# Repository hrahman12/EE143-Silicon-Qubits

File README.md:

# Atom-by-Atom Silicon: Building Quantum Processors from Single Dopant Atoms

EE143 (Microfabrication Technology) tutorial deck, 15 min. A device profile of STM-patterned P and As dopant qubits, featuring the work of Neil J. Curson (UCL).

- **Deck:** `deck/atom_by_atom_silicon.pptx` (editable, 16:9, 10 × 5.625 in) and `deck/atom_by_atom_silicon.pdf`
- **Speaker notes:** in the .pptx and in `notes/speaker_notes.md` (with a 15-minute timing plan)
- **Facts:** every number comes from `REFERENCES.md` (transcribed from `notes/reference_pack.pdf`); see `qa/fact_check.md`

## Rebuild

```bash
npm install                                  # pptxgenjs 3.12.0, image-size 1.1.1
pip install matplotlib numpy pillow pymupdf  # figure scripts
python3 figures/src/make_figures.py          # crops + original diagrams -> figures/final/
npm run build                                # node build_deck.js, strip zip folder entries, export PDF (needs LibreOffice)
```

QA render: `pdftoppm -jpeg -r 110 deck/atom_by_atom_silicon.pdf qa/render/s` (renders are git-ignored).

### Re-downloading raw figures
`python3 figures/src/fetch_pmc.py` pulls figure images, article XML (licence text) and metadata from the PMC Open Access bucket. The article PDFs are git-ignored to keep the repo small; the images extracted from them (`figures/raw/*/pdfimg/`, `page*_300dpi.png`) are committed. To re-extract, download:
- PMC PDFs: `https://pmc-oa-opendata.s3.amazonaws.com/<PMCID>.1/<PMCID>.1.pdf`
- Schofield2025: `https://arxiv.org/pdf/2501.04535v2`
- DAnna2023: UCL Discovery 10167842 (CC BY published version)

## Simulations and animations
`npm run sim` (QuTiP 5) runs `figures/src/simulate_qubits.py`:
- fits the Reiner2024 donor Hamiltonian to the 14 ESR/NMR lines of Thorvaldson2025, recovering A = 6.05/67.97/102.99 MHz;
- simulates the conditional Rabi drive and Grover search;
- renders the fabrication, yield Monte Carlo and cover animations.

Animated GIFs play in PowerPoint and Keynote; the PDF shows each first frame. `qa/add_transitions.py` adds fade transitions after the build. No real quantum hardware was run.

## Web preview
`python3 qa/build_preview.py <dir>` composites each embedded GIF into its LibreOffice slide render (animated WebP) and writes `slides.json`. That folder plus `index.html` is the published preview page, republished after each deck change.

## Layout system
`build_deck.js` defines the theme once (Arial; ink #1F2A36, muted #5B6770, P #D9731A, As #0F9FA0, fixed material legend) and eight slide masters (TITLE, SECTION, TITLE_ONLY, FIG_TEXT, TWO_FIG, TABLE, PROCESS, REFS) with named `title` and `src` placeholders, footer and slide number. Sections: Intro, Motivation, Process, Results, Scaling, Prototype, Wrap-up, Backup. Charts (array yield, write speed on a log axis, Poisson ion statistics, thermal budget) are native PowerPoint charts.

## Story and slides (four acts)
Intro → Act 1 Why single atoms → Act 2 How it is built → Act 3 Does it work → Act 4 How it scales → Wrap-up. Each slide carries an act label.

## Exact paper specs
Diagrams are drawn from verbatim specs collected in `notes/specs/` (one table per paper group, each value with its quote and location): to-scale D'Anna 2023 stack, Stock 2020 Fig. 4e temperature program, Si(001) geometry (a = 3.84 Å, dimer bond 2.357 Å, Si–H 1.51 Å), Schofield 2003 sites, Kane 2000 operating point, prototype layout from Stock 2024 + Edlbauer 2025. New sources beyond the pack: Jakob2022, Reiner2024, Namboodiri2024, DAnna2026, Kiczynski2022, Kane2000, OBrien2001, Ren2016, Xiang2025 (see `notes/specs/additional_sources.md`).

## Slides (original outline, now reordered)
1 Title · 2 Device at a glance · 3 Timeline · 4 Why a donor · 5 Why not implantation · 6 Neil J. Curson · 7 11-step process flow (EE143 module per step) · 8–13 Steps 1–11 (cross-section + legend + step tracker) · 14 Did it work (+ EE143 sheet-resistance check) · 15 Landmarks · 16 Yield problem (+ Monte Carlo) · 17 Arsenic fix · 18 Beyond Si:P · 19 Processors · 20 Simulator · 21 Throughput wall · 22 EUV scaling · **23 Our prototype (3D render + yield model)** · **24 Prototype traveler mapped to EE143** · 25 Takeaways · 26 References · Backup: alternate titles

Slides 23–24 go beyond the outline: an original 2×2 As register design and its traveler, built only from published recipes.

## Reproduced vs original images
**Reproduced (CC BY 4.0, credited on the slide):** Stock2024 Figs. 1, 3; Schofield2025 §2.2, §2.4, §3.2, §4.1, §5.3 figures; Constantinou2024 Fig. 5; Constantinou2023 Fig. 2; D'Anna2023 Fig. 2; Stock2020 Figs. 3, 4; Hofmann2023 Fig. 1a; Lundgren2023 Fig. 1; Thorvaldson2025 Fig. 4b; Edlbauer2025 Fig. 1a,b; Wang2022 Fig. 1. Licences were checked in each article's own XML; Stock2020 (ACS AuthorChoice CC-BY) and Tseng2023 (CC BY 4.0) included.

**Original (code in `figures/src/make_figures.py`, or native shapes and charts):** Kane-style cross-section (after Kane1998), 3D Si(001):H surface renders, step cross-sections, process icons, overgrowth temperature program, spin-level diagram, 2003/2012 landmark schematics (after Schofield2003 / Fuechsle2012), Monte Carlo array outcomes, 3D yield surface, prototype 3D render, timelines, all charts. No paywalled or CC BY-NC-ND figure is embedded, and no micrograph or data plot is generated. Full list: `figures/manifest.csv`.

## QA status
- Rendered with LibreOffice and checked slide by slide (overflow, overlaps, margins, title position).
- Anthropic pptx-skill `validate.py`: all validations passed.
- Speaker notes: 98–130 words on every slide.
- `qa/fact_check.md`: every number on the slides mapped to its Key-numbers row and key; derived values marked.
- `qa/text_dump.txt`: full text and notes dump via python-pptx.

## Open items
See `qa/open_items.md`. Main ones: the `reference_decks/` folder wasn't supplied, so style comes from the measurements in the reference pack; confirm the talk date (shown as "Fall 2026"); and a few outline items had no source and were left off.

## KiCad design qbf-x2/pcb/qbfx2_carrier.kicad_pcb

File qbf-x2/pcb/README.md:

# QBF-X2 cryogenic RF carrier PCB (rev B, 2026-11-26)

A 6-layer Rogers RO4003C / RO4450F carrier for the 10 x 10 mm QBF-X2 superconducting die. The die sits in a
10.30 mm through-window on a pedestal of the copper sample-holder base, with its top
flush with the board. It is wire bonded to 32 landing pads that follow `../circuits/die_pads.json` (rev B), the
chip-to-board contract.

- **8 fast flux lines = 8 differential pairs** (`<name>_P` / `<name>_N`, 16 SMP jacks). On the chip each fast line is
  one floating loop: P runs out along its rail, N comes back on the far side of the launch strip, with no ground
  return. Each leg is driven by its own 50-ohm coax from complementary AWG outputs.
- **2 readout lines** (RO_IN, RO_OUT): single-ended 50-ohm grounded CPW, unchanged from rev A.
- **8 DC lines**: striplines on In2 to on-board RC filters next to a micro-D connector (J11), unchanged in function.

All RF lines are mask-free grounded CPW on the top layer over the solid In1 plane. Everything is generated by Python
from `carrier_params.py`; nothing was drawn by hand. KiCad 7.0.11 (`kicad-cli` and the `pcbnew` module) fills the
zones, runs DRC and writes every fabrication output.

| | |
|---|---|
| Board | 66 x 66 mm (rev A: 52 x 52), 1.50 mm, 6 Cu layers, through vias only |
| Parts | 52 schematic parts (47 on the PCBA), 5 board-only (3 fiducials, 2 dowel holes) |
| Nets | 43: 16 fast-line legs (8 pairs), 2 readout, 24 DC (8 die-side, 8 connector-side, 8 filter nodes), GND |
| Vias | 1421: 1393 GND stitching / fences / launch cages, 16 DC transitions, 12 filter-cap GND |
| DRC (pcbnew 7.0.11) | **0 violations, 0 unconnected, 0 footprint errors** (KiCad's own diff-pair, skew and length rules included) |
| Schematic vs PCB | **0 mismatches** (52 components, 144 pads) |
| Differential pairs | Z_odd 51.9 ohm (closed form) / 47.9 ohm (2D field solve, 35 um Cu); field solve: Z_diff 95.8 ohm, Z_even 51.4 ohm, Z_cm 25.7 ohm, k = 0.035 |
| Intra-pair skew | max 0.0002 mm = 0.0011 ps (limit 0.10 mm ~ 0.5 ps) |
| A/B pair match | max 0.0002 mm (limit 0.20 mm) |
| Single-ended GCPW | rf_calc formula 51.98 ohm; 2D field solve (35 um Cu) 47.66 ohm; target 50 +/-5 % |
| Filters | gate 596 Hz (<= 10 kHz); load 17.7 MHz into the load loop, 8.84 MHz open |

## What changed from rev A

| | rev A | rev B |
|---|---|---|
| Die contract | 24 pads, 8 single-ended fast lines | 32 pads (`circuits/die_pads.json` rev B): 8 P/N pad pairs, 0.50 mm apart, 1.40 mm between pair centres |
| Fast lines | 50-ohm GCPW to 8 SMP jacks | edge-coupled GCPW pairs to 16 SMP jacks (two per pair, side by side) |
| Board | 52 x 52 mm | 66 x 66 mm; SMP columns at x = +/-26.5 mm, 8 jacks per side at a 6.5 mm pitch |
| Filter bank / J11 | channel vias at y = 9, J11 at y = 19 | moved north (vias y = 16, J11 y = 26) to clear the TRAP pairs; same circuit and routing topology |
| Designators | SMP J1-J10, micro-D J11 | SMP J1-J10 and J12-J19 (18 jacks), micro-D stays J11 |
| DRC rules | A/B skew groups | per-pair width / gap / uncoupled / skew rules plus A/B length windows (below) |

The reason for the change is on the chip: a fast line that is one floating loop has no ground return, so its
crosstalk into the other rail of the same qubit drops from 9-17 % to 5.5-7 % (2D cross-section solve of the die),
and common-mode / ground-loop current cannot drive flux through it.

## Files

| Path | What |
|---|---|
| `carrier_params.py` | single source of truth: geometry, stackup, rules, pair geometry, filter values, parts |
| `build_carrier.py` + `carrier_lib/` | writes the KiCad project from scratch (schematic, libraries, 3D models, routed board, rules) |
| `carrier_lib/diffpair.py` | differential-pair geometry: concentric bends, symmetric opening, arc-only tuning bumps, split, KiCad 7 coupling helpers |
| `carrier_lib/fd2d.py` | 2D field solver (single GCPW and odd/even modes of the coupled pair) and the coupled closed-form estimate |
| `finalize_carrier.py` | KiCad zone fill + DRC (pcbnew) |
| `check_carrier.py` | schematic-vs-PCB, ERC substitute, impedance (single-ended and pairs), lengths and skew, filters, DRC fault injection |
| `make_outputs.py`, `render_3d.py`, `make_readme.py` | BOM, drawings, previews, 3D renders, this README |
| `export_carrier.sh` | runs everything: rebuilds every file below |
| `qbfx2_carrier.kicad_pro/.kicad_sch/.kicad_pcb/.kicad_dru` | the KiCad 7 project (zones filled) |
| `qbfx2.kicad_sym`, `qbfx2.pretty/`, `sym-lib-table`, `fp-lib-table`, `3dmodels/` | project libraries (inline copies are in the sheet and the board) |
| `fab/gerbers/` | Gerber X2: 6 copper, 2 mask, 2 paste, 2 silk, Edge.Cuts, fab-notes layer, `.gbrjob` |
| `fab/drill/` | Excellon PTH + NPTH (mm, origin = board lower-left) and drill-map PDFs |
| `fab/assembly/qbfx2_carrier-pos.csv` | pick-and-place (mm, both sides, origin = board lower-left) |
| `fab/qbfx2_carrier_bom.csv` | BOM with manufacturer, MPN, MPN status |
| `fab/qbfx2_carrier-schematic.pdf` | schematic (A3) |
| `fab/qbfx2_carrier-fab_drawing.pdf` | fabrication drawing: outline + dimensions, stackup, impedance and drill tables, fab notes, then drill maps |
| `fab/qbfx2_carrier-assembly.pdf` | assembly drawing: 2:1 top detail, wire-bond diagram, notes, BOM summary, J11 pinout, RF lengths |
| `fab/qbfx2_carrier.step` | 3D STEP of the assembled board (KiCad export with the generated OCP models) |
| `fab/qbfx2_carrier.net` | schematic netlist (KiCad s-expression) |
| `fab/previews/` | PNG previews: top/bottom, each copper layer, die area, In2 routing, drawings, 3D renders |
| `reports/` | DRC report, all check reports, `check_summary.json`, build model, logs |

## Board

**Die interface.** U1 has one landing pad per die pad, pads 1-32 = die launcher ids, 0.10 mm
from the window edge and laterally aligned with the die pads, so every bond is straight (0.77 mm from
the die pad centre to the bond foot, angle 0.0 deg). The lands of the differential pairs are
0.29 x 0.60 mm on the die's 0.50 mm pitch (P-N gap 0.21 mm,
gap to ground 0.17 mm; minimum clearance 0.15 mm); all other lands are
0.39 x 0.60 mm. The window is 10.30 mm (0.15 mm clearance),
with R0.60 corner reliefs. The ground between landing pads is exposed (F.Mask openings over GND only)
for ground bonds where the strip is wide enough: on the N/S rows, at the corners and between each TRAP pair and its LOAD
land. Between two pairs the ground strip at the lands is only 0.27 mm wide, so it stays under mask (the fast lines are
floating loops on the chip and do not return through the die ground).

**Differential pairs (8 fast flux lines).**
- Cross-section (routed): two legs w 0.39 mm, P-N gap 0.65 mm (leg pitch 1.04 mm), gap
  0.17 mm to the coplanar ground, over 0.203 mm RO4003C to the In1 plane. No ground copper and no vias between
  P and N: an F.Cu keepout per pair (`DIFF_<pair>_no_gnd_no_via`) blocks the pour and vias; the via fences run on the
  outside of each pair only.
- Loose coupling on purpose: each leg is a 50-ohm line for its own coax, so Z_odd = 50 ohm and Z_even stays near 50 ohm
  (k = 0.035). The legs use the same width and ground gap as the single-ended lines, so the split into two
  single-ended legs at the jacks is a smooth transition.
- Breakout at the die: the die pads are 0.50 mm apart and the pairs 1.40 mm apart, which leaves no room for the routed
  cross-section. From the lands to the first bend each pair runs as w 0.29 / gap 0.21 mm (leg pitch 0.50 mm,
  so the lands and the coupled pair line up and the bonds stay straight). Right after the first bend both legs make
  mirror-image S-jogs (R 1.0 mm) out to the routed spacing and the width steps to 0.39 mm.
- Route (west-top quadrant; the others are mirror images): straight breakout, bend B1 away from the die axis
  (60.3 deg for TRAP, 45 deg for ACC; the TRAP angle is tan = 7/4 so that both legs lie on an exact nm lattice),
  diagonal, bend B2 back to the die-normal direction, straight, then the split: each leg turns away from its partner
  (45-degree jogs, R 1.0 mm) and runs straight into its own SMP jack. Every bend is a pair of concentric
  tangent arcs (inner leg radius R - c/2, outer R + c/2), so the pair stays symmetric through the bend.
- Jacks: two SMP jacks per pair, side by side 6.5 mm apart in the column at x = +/-26.5 mm
  (ACC pairs at |y| = 3.25 / 9.75 mm, TRAP pairs at |y| = 16.25 / 22.75 mm).
  West column top to bottom: J1 TRAP_A0_P, J2 TRAP_A0_N, J3 ACC_A0_P, J4 ACC_A0_N, J5 ACC_A1_P, J6 ACC_A1_N, J7 TRAP_A1_P,
  J8 TRAP_A1_N; east column: J9 TRAP_B1_P, J10 TRAP_B1_N, J12 ACC_B1_P, J13 ACC_B1_N, J14 ACC_B0_P, J15 ACC_B0_N, J16 TRAP_B0_P,
  J17 TRAP_B0_N. RO_IN = J18, RO_OUT = J19. The pair is coupled from the lands to the split; the split is
  6.54 mm (TRAP) / 6.54 mm (ACC) per leg.
- Length matching: a concentric bend of angle theta at leg pitch c makes the inner leg shorter by c * theta. B1 is taken
  at the breakout pitch (0.50 mm) and B2 at the routed pitch (1.04 mm), so they do not cancel. Each mismatch is
  compensated next to the bend that causes it, with small symmetric arc-only bumps (arcs +a, -2a, +a, R 0.30 mm)
  on the shorter leg, bulging away from its partner: the outer leg right after the opening for B1, the inner leg next to
  B2 (just before it for TRAP, just after it for ACC). TRAP: -60.3 deg at leg pitch 0.50 mm -> TRAP_A0_P short by 0.526 mm; +60.3 deg at leg pitch 1.04 mm -> TRAP_A0_N short by 1.094 mm. Bumps: TRAP_A0_P: 1 x +0.526 mm (height 0.51 mm, span 1.19 mm); TRAP_A0_N: 2 x +0.547 mm (height 0.53 mm, span 1.19 mm). ACC: -45.0 deg at leg pitch 0.50 mm -> ACC_A0_P short by 0.393 mm; +45.0 deg at leg pitch 1.04 mm -> ACC_A0_N short by 0.817 mm.
  Bumps: ACC_A0_P: 1 x +0.393 mm (height 0.43 mm, span 1.15 mm); ACC_A0_N: 2 x +0.408 mm (height 0.44 mm, span 1.16 mm). The running P-N difference returns to zero within 4.9 mm (TRAP) /
  4.3 mm (ACC) of every bend.
- Mask: every leg has its own mask-free corridor (trace + gaps); a 0.14 mm LPI web on the pair centre line separates
  the two (KiCad flags one aperture that exposes two nets). In the routed section that leaves 0.16 mm bare next to each
  leg and LPI on the middle 0.33 mm of the P-N gap; the field solve includes it.

**Readout lines (2).** Single-ended GCPW on F.Cu over the solid In1 plane, w 0.39 mm, gap 0.17 mm,
tangent-arc bends R 1.0 mm, GND vias every 1.0 mm on both sides at 0.625 mm from the line centre, to J18/J19
on the south side. Each SMP has a GND via cage (3 under the body, 9 around it), a 0.75 mm centre pad and a 1.65 mm anti-pad.

**DC lines (8).**
- Each landing pad has a short F.Cu stub to a via, then a 0.15 mm stripline on In2 between the In1 and In3 planes.
- The south lines (GATE_BSB_*) and LOAD_A1/LOAD_B0 reach the north through an In2 corridor under the bond-pad ring; the
  planar order means nothing crosses. Rev B: the LOAD lands moved out to |y| = 3.5 mm, so the bottom LOAD lines now join
  their corridor with a 45-degree segment, clear of the GATE_BSB detour around the window corner.
- They end at 8 filter channels on the top side, next to J11.
- J11 pinout: 1 LOAD_A0, 2 LOAD_A1, 3 GATE_BSB_AN, 4 GATE_BSA_PREP, 5 GATE_BSA_AN, 6 GATE_BSB_PREP, 7 LOAD_B0, 8 LOAD_B1; 9-15 and the shell are GND.

**Mechanics.**
- 4 x M2.5 plated holes (GND) at +/-29.5 mm.
- 2 x 1.60 mm NPTH dowel holes align the window to the base pedestal.
- 3 fiducials.
- The bottom copper is a continuous GND plane; B.Mask is opened 2 mm along the edge for contact with the base.
- The J11 tails and their solder fillets (DC signals) come through to the bottom. The copper base therefore needs a
  relief pocket, at least 1.5 mm deep, under the tail field (x -11..+11 mm, y +24..+30 mm
  from the die centre). Otherwise the DC lines short to ground.

### Stackup (defined in the board file, `setup/stackup`)

| Layer | Type | Material | t (mm) | er | tan d | Use |
|---|---|---|---|---|---|---|
| F.Mask | mask | LPI solder mask | 0.020 | 3.8 | 0.025 | green LPI; open over RF lines + bond band |
| F.Cu | copper | Cu 1 oz (finished) | 0.035 |  |  | RF GCPW, bond pads, parts, GND pour |
| diel1 | core | Rogers RO4003C | 0.203 | 3.55 | 0.0027 | core 1 (8 mil); GCPW dielectric |
| In1.Cu | copper | Cu 0.5 oz | 0.018 |  |  | solid GND: GCPW reference plane |
| diel2 | prepreg | Rogers RO4450F | 0.203 | 3.52 | 0.004 | 2 x 4 mil plies |
| In2.Cu | copper | Cu 0.5 oz | 0.018 |  |  | DC routing (stripline between In1/In3) + GND fill |
| diel3 | core | Rogers RO4003C | 0.508 | 3.55 | 0.0027 | core 2 (20 mil) |
| In3.Cu | copper | Cu 0.5 oz | 0.018 |  |  | solid GND |
| diel4 | prepreg | Rogers RO4450F | 0.203 | 3.52 | 0.004 | 2 x 4 mil plies |
| In4.Cu | copper | Cu 0.5 oz | 0.018 |  |  | solid GND |
| diel5 | core | Rogers RO4003C | 0.203 | 3.55 | 0.0027 | core 3 (8 mil) |
| B.Cu | copper | Cu 1 oz (finished) | 0.035 |  |  | solid GND; contacts the sample-holder base |
| B.Mask | mask | LPI solder mask | 0.020 | 3.8 | 0.025 | opened along the board perimeter (base contact) |

**Why RO4003C:**
- Low loss: tan d 0.0027.
- Stable Dk.
- The glass-reinforced hydrocarbon/ceramic does not cold-flow, unlike PTFE.
- Processes like FR-4, so a symmetric 3-core build needs one lamination and through vias only.
- The room-temperature design Dk 3.55 is used. How Dk and loss change at 10 mK is not modelled here.

## Design rules

The board minima are set in `.kicad_pro`:
- clearance 0.15 mm, track 0.12 mm
- via 0.45 / 0.20 mm, annular ring 0.125 mm
- hole-to-hole 0.25 mm, hole clearance 0.20 mm
- copper-to-edge 0.10 mm (used only at the die window: landing pads and exposed ground band)
- mask web 0.10 mm

Net classes are assigned by pattern:

| Net class | Patterns | Width | Clearance | Diff pair |
|---|---|---|---|---|
| RF_DIFF | TRAP_*, ACC_* | 0.39 mm | 0.17 mm | width 0.39 / gap 0.65 mm (KiCad pairs `_P` / `_N`) |
| RF_50 | RO_* | 0.39 mm | 0.17 mm (the CPW gap) | |
| DC | LOAD_*, GATE_*, Net-* | 0.20 mm | 0.20 mm | |
| Default | GND | | 0.15 mm | |

Custom rules in `.kicad_dru` (KiCad 7 syntax, checked by KiCad's own DRC):
- RF: width 0.38-0.40 mm for RO; gap to GND >= 0.17 mm for every RF net; RF to other signals >= 0.40 mm (except P to N
  of the same pair: `!AB.isCoupledDiffPair()`); RF only on F.Cu and no vias on RF nets.
- `DIFF_intra_pair_clearance`: P to N >= 0.20 mm.
- `DIFF_routed` (`A.inDiffPair('*') && A.Width >= 0.34mm`): track width 0.39 +/-0.01,
  `diff_pair_gap` 0.65 +/-0.01 mm, `diff_pair_uncoupled` <= 10.5 mm.
- `DIFF_breakout` (width below that): track width 0.29 +/-0.01, `diff_pair_gap` 0.21 +/-0.01 mm,
  `diff_pair_uncoupled` <= 1.2 mm.
- `<pair>_intra_pair_skew` (one rule per pair, `A.inDiffPair('<pair>')`): `skew` max 0.050 mm. KiCad 7 defines
  skew as the net length minus the average of the nets in the rule, so this is |L_P - L_N| <= 0.10 mm.
- `TRAP_A_vs_B_length`, `ACC_A_vs_B_length`: every leg within +/-0.10 mm of its type's nominal length, so
  corresponding A and B pairs agree within 0.20 mm (a length rule, because a net can only be in one skew rule).
- DC: In2 width >= 0.15 mm, clearance 0.20 mm. Via geometry. Tracks and vias >= 0.30 mm from any edge.

A keepout pulls the inner-layer copper back 0.30 mm from the die window.

**KiCad 7.0 diff-pair details (found while building this board, worked around in `carrier_lib/diffpair.py`):**
- KiCad's coupling test treats two straights as coupled only if they are parallel to 1 nm in the file's integer-nm
  coordinates. The pair legs are therefore written with nm resolution, and every straight is snapped to an exact lattice
  direction (horizontal, 45 deg, or 7:4 for the TRAP diagonal).
- A straight whose end touches an arc or a pad is counted as uncoupled, so every straight next to an arc or a land starts
  with a separate 0.25 mm coupling stub.
- Each straight is coupled with one partner straight only, so the stubs are tilted by 10 nm (never parallel to anything)
  and the legs are split at the same stations around each bump.
- With this, KiCad's own uncoupled length is 1.00 mm in the breakout (the four stubs) and
  9.86 mm (TRAP) / 9.79 mm (ACC) in the routed section: the stubs, the bump
  spans and the split to the two jacks, which is uncoupled by design.

## Checks and results (all from the last `./export_carrier.sh` run)

| Check | Result | Report |
|---|---|---|
| DRC, pcbnew 7.0.11 after KiCad zone fill | 0 violations, 0 unconnected, 0 footprint errors (library parity included) | `reports/drc_report.txt` |
| DRC self-test (9 faults injected on copies of the board) | 9/9 detected: the rules are live | `reports/drc_selftest.txt` |
| Schematic vs PCB (kicad-cli netlist vs pcbnew pads) | 0 mismatches over 52 components / 144 pads / 43 nets | `reports/sch_vs_pcb.txt` |
| ERC substitute | 0 issues: every net has >= 2 pins, no floating pin, 32/32 U1 pins on their die_pads.json net, GND has a PWR_FLAG, BOM fields present | `reports/erc_report.txt` |
| Differential pairs, routed (closed form and field solve both required) | Z_odd 51.93 / 47.91 ohm; as built P-N gap 0.650-0.650 mm, gap to GND 0.170-0.171 mm | `reports/impedance_table.txt` |
| Differential pairs, breakout (field solve required) | Z_odd 48.15 ohm | same |
| Single-ended GCPW (rf_calc formula, required) | 51.98 ohm drawn; 52.00-52.06 ohm using the gap measured in the filled zones | same |
| Single-ended GCPW (2D field solve, cross-check) | 47.66 ohm with 35 um copper; validation in the thin-copper limit 51.46 ohm | same |
| Reference plane | In1 under every RF line: 100.00 % coverage | same |
| Intra-pair skew | max 0.0002 mm (0.0011 ps), limit 0.10 mm | `reports/length_report.txt` |
| A/B matching | max 0.0002 mm, limit 0.20 mm | same |
| KiCad uncoupled length | 9.86 / 9.79 mm routed (limit 10.5), 1.00 mm breakout (limit 1.2) | `reports/drc_selftest.txt` |
| Filter cut-offs (values read back from the schematic) | all 8 channels PASS | `reports/filter_report.txt` |

**Differential pair impedance.** Two independent models of the same cross-section:
- closed form (`fd2d.closed_form_coupled`): zero-thickness coupled conductor-backed CPW from partial capacitances. The air
  half space is mapped with w = z^2 (odd mode: electric wall on the symmetry plane, even mode: magnetic wall), the
  substrate slab with the In1 plane with t = cosh(pi z / h); each part is eps K(k)/K(k') with k from the cross ratio of
  the conductor edges. For s -> 0 its even mode equals `rf_calc.gcpw_z0` of a 2w strip exactly.
- field solve (`fd2d.solve_coupled`): finite differences on half the section, odd mode = V = 0 on the symmetry plane,
  even mode = Neumann; 35 um copper, LPI on the outer grounds and on the centre-line web.

| Section | w / s / g (mm) | Model | Z_odd | Z_even | Z_diff | Z_cm | k |
|---|---|---|---|---|---|---|---|
| routed | 0.39 / 0.65 / 0.17 | closed form | 51.93 | 57.08 | 103.9 | 28.5 | 0.047 |
| routed | | field solve, 35 um | 47.91 | 51.42 | 95.8 | 25.7 | 0.035 |
| breakout | 0.29 / 0.21 / 0.17 | closed form | 54.95 | 70.87 | 109.9 | 35.4 | 0.127 |
| breakout | | field solve, 35 um | 48.15 | 65.24 | 96.3 | 32.6 | 0.151 |

- Routed pair: both models put Z_odd inside 50 ohm +/-5 % (+3.9 % and
  -4.2 %), the same way the single-ended line is centred between its two models.
  The field solve gives Z_even 51.4 ohm (+2.8 %), i.e. loose coupling.
  The closed form reads the even mode higher; its partial-capacitance split is least accurate for a P-N gap that is wide
  compared with h (s = 3.2 h). The field solve was checked against grid, lid height and ground width (< 0.3 %).
- Breakout: the field solve (as built) gives Z_odd 48.2 ohm. The zero-thickness closed form reads
  54.9 ohm because the 35 um copper sidewalls across the 0.21 mm P-N slot add capacitance; in the
  thin-copper limit the two agree (54.4 vs 54.9 ohm). The breakout is tighter coupled
  (k 0.15); it is a short section forced by the die pad pitch.

**Lengths.** The copper length per net is read from the routed board with pcbnew, from the track start at the landing
pad to the SMP pin. The delay uses the odd-mode eeff of the field solve (5.252 ps/mm).

| Pair | Jacks P / N | L_P (mm) | L_N (mm) | P-N (mm) | P-N (ps) | |
|---|---|---|---|---|---|---|
| TRAP_A0 | J1 / J2 | 32.3448 | 32.3446 | +0.0002 | +0.0010 | PASS |
| ACC_A0 | J3 / J4 | 24.6291 | 24.6293 | -0.0001 | -0.0006 | PASS |
| ACC_A1 | J5 / J6 | 24.6292 | 24.6292 | +0.0000 | +0.0000 | PASS |
| TRAP_A1 | J7 / J8 | 32.3447 | 32.3449 | -0.0002 | -0.0011 | PASS |
| TRAP_B1 | J9 / J10 | 32.3449 | 32.3447 | +0.0002 | +0.0011 | PASS |
| ACC_B1 | J12 / J13 | 24.6292 | 24.6292 | -0.0000 | -0.0001 | PASS |
| ACC_B0 | J14 / J15 | 24.6293 | 24.6291 | +0.0001 | +0.0006 | PASS |
| TRAP_B0 | J16 / J17 | 32.3446 | 32.3448 | -0.0002 | -0.0010 | PASS |

| A / B pairs | mean dL (mm) | (ps) | dL of P (mm) | dL of N (mm) | |
|---|---|---|---|---|---|
| TRAP_A0 / TRAP_B0 | 0.0000 | 0.0000 | 0.0002 | 0.0002 | PASS |
| TRAP_A1 / TRAP_B1 | 0.0000 | 0.0000 | 0.0002 | 0.0002 | PASS |
| ACC_A0 / ACC_B0 | 0.0000 | 0.0000 | 0.0001 | 0.0001 | PASS |
| ACC_A1 / ACC_B1 | 0.0000 | 0.0000 | 0.0000 | 0.0000 | PASS |

TRAP legs are 32.345 mm and ACC legs 24.629 mm; the difference is the same on both sides and is
not part of the A/B requirement. RO_IN and RO_OUT are both 13.7208 mm.

**Filters.** The cut-offs are computed from the schematic values (`carrier_lib/filters.py`).

| Lines | Topology | Values | -3 dB | Requirement |
|---|---|---|---|---|
| GATE_BSA_PREP/AN, GATE_BSB_PREP/AN | 2-stage RC ladder | R1 = R2 = 10 kOhm, C1 = C2 = 10 nF C0G | 596 Hz (594 Hz with a 50 ohm source); single stage 1/2piRC = 1592 Hz | <= 10 kHz |
| LOAD_A0/A1/B0/B1 | R-C-R tee | R1 = R2 = 1.0 kOhm, C = 18 pF C0G | 17.68 MHz into the 1 nH on-chip load loop (current drive), 8.84 MHz into a high-impedance load | 10-20 MHz, >= 5 MHz for the 1 us ramp |

**DRC self-test** (`reports/drc_selftest.txt`): one fault per copy of the board.

| Fault | KiCad DRC |
|---|---|
| F1_rf_width | detected |
| F2_cpw_gap | detected |
| F3_skew | detected |
| F4_via_on_rf | detected |
| F5_open_dc | detected |
| F6_diff_width | detected |
| F7_diff_pair_gap | detected |
| F8_via_between_legs | detected |
| F9_uncoupled_probe | detected |

## Parts and cryogenic notes

| Refs | Qty | Value | Manufacturer | MPN | Status |
|---|---|---|---|---|---|
| C1 C2 C11 C12 | 4 | 18p C0G | Vishay Vitramon | VJ0603A180JCAAJ | to confirm |
| C3 C4 C5 C6 C7 C8 C9 C10 | 8 | 10n C0G | Vishay Vitramon | VJ0603A103JCAAJ | to confirm |
| H1 H2 H3 H4 | 4 | M2.5 | - | - | mechanical |
| J1 J2 J3 J4 J5 J6 J7 J8 J9 J10 J12 J13 J14 J15 J16 J17 J18 J19 | 18 | SMP-MSLD-PCS-NM | Amphenol RF | SMP-MSLD-PCS-NM | confirmed |
| J11 | 1 | MWDM2L-15PCBRP-.110 | Glenair | MWDM2L-15PCBRP-.110 | confirmed |
| R1 R2 R3 R4 R13 R14 R15 R16 | 8 | 1k | Vishay Dale Thin Film | PNM0603E1001BST5 | confirmed |
| R5 R6 R7 R8 R9 R10 R11 R12 | 8 | 10k | Vishay Dale Thin Film | PNM0603E1002BST5 | confirmed |
| U1 | 1 | QBF-X2 | QBF-X2 project | QBF-X2 die rev per circuits/ | customer supplied |

- **"confirmed"** means a distributor or manufacturer listing for the exact part number was found during the design
  (November 2026). The SMP jack, the micro-D and both resistors are confirmed.
- **"to confirm"**: the two Vishay VJ Non-Magnetic C0G capacitors. The codes follow the series ordering scheme
  (termination C = non-magnetic Cu barrier), but neither exact code was found in a listing. Check them before ordering.
- **Non-magnetic where it matters:** Amphenol RF `-NM` SMP (BeCu/Au, LCP); Vishay PNM thin-film resistors; C0G/NP0
  capacitors with Cu-barrier terminations; no ferrite; the micro-D shell finish is to be specified non-magnetic;
  mounting screws in brass or Ti.
- **Surface finish:** Ni-free. Preferred is EPAG (electroless Pd + immersion Au) or electrolytic soft Au >= 0.5 um
  directly on Cu. Not ENIG: its 3-6 um electroless Ni(P) can be ferromagnetic and, next to a flux-based die, traps
  vortices, shifts flux offsets and adds noise and loss at 10 mK.
- **Solder:** SAC305 or SnPb. Sn-based solder superconducts below 3.7 K; the nearest joints (SMP, filters) are more
  than 7 mm from the die.

## Rebuild

```bash
cd qbf-x2/pcb
./export_carrier.sh              # project + checks + all outputs + 3D render (render a few minutes on 2 threads)
./export_carrier.sh --no-render  # same, keeps the existing render PNGs
python -m pytest ../tests/test_carrier.py   # rebuild in a temp dir + DRC + checks
```

Requirements: KiCad 7.0.x (`kicad-cli` and the `pcbnew` Python module); Python 3 with shapely, numpy, scipy, pillow,
pypdf and cadquery-ocp; poppler (`pdftoppm`); optional: the `bpy` module, for the render.

To change the design, edit `carrier_params.py`. The generated KiCad source files are byte-identical between rebuilds,
because the UUIDs come from a seeded stream. The generator asserts that `die_pads.json` still has the pad arrangement
the routing was designed for (rev B: 6 / 10 / 6 / 10 pads, P/N pairs 0.50 mm apart, 1.40 mm between pairs); if the
contract changes, the build stops with a message.

## Opening it in Altium Designer

Altium Designer has a KiCad importer: *File > Import Wizard > KiCad Design Files*. Point it at
`qbfx2_carrier.kicad_pro`. Do not expect the KiCad custom rules (`.kicad_dru`) to be translated: re-enter the rules
listed above as Altium design rules (clearance, width, differential-pair width/gap, matched length within each pair and
between A/B pairs, net-class scopes), and define the 8 differential pairs (`<name>_P` / `<name>_N`) in Altium's
differential-pair editor. The import was not tested here, because Altium does not run on Linux.

**Native Altium libraries** are in `altium/`: `QBFX2_Carrier.PcbLib`, `QBFX2_Carrier.SchLib` and
`QBFX2_Carrier.LibPkg`, written by [altium-designer-mcp](https://github.com/embedded-society/altium-designer-mcp) from
this board's own footprints, symbols, STEP models and BOM. See `altium/README.md`. The PCB-editor views
`altium/views/altium_style_*.png` show the routed board in Altium's colours, including a close-up of a differential
pair with its tuning bumps (`altium_style_diff_pair.png`).

## Not done, not verified, to confirm

**Not verified (no full-wave EM simulation):**
- the SMP launches, the wire-bond transition and the die-window cavity;
- the pair bends, the opening transition, the tuning bumps and the split (designed so the odd mode sees ~50 ohm
  everywhere; the bumps and the split are short single-leg detours);
- fence and box modes.

Expect the bonds (about 0.8 mm, 2 in parallel) to add roughly 0.4-0.5 nH per leg, which is noticeable at 10 GHz.

**Land patterns to confirm against vendor drawings:** SMP (Amphenol SMP-MSLD-PCS-NM: generic pads; 6.5 mm jack pitch
assumes the mating cable plugs fit side by side) and micro-D (Glenair MWDM2L-15PCBRP-.110).

**Part numbers:** the 2 capacitor codes are "to confirm" (see above).

**Not exported, because KiCad 7.0.11 cannot write them:** ODB++, IPC-2581 and the IPC-D-356 netlist. KiCad 7 also has
no command-line ERC; `check_carrier.py` implements the substitute described above.

**Not designed here:** the copper sample-holder base (die pedestal 0.957 mm high for a 20 um varnish layer, J11 relief
pocket, lid, dowels), thermal anchoring, the cryostat wiring (16 coax for the fast pairs, phase-matched in pairs), and a
check of the RO4003C Dk at 10 mK.

The 3D models are simplified envelopes, for fit and renders only.

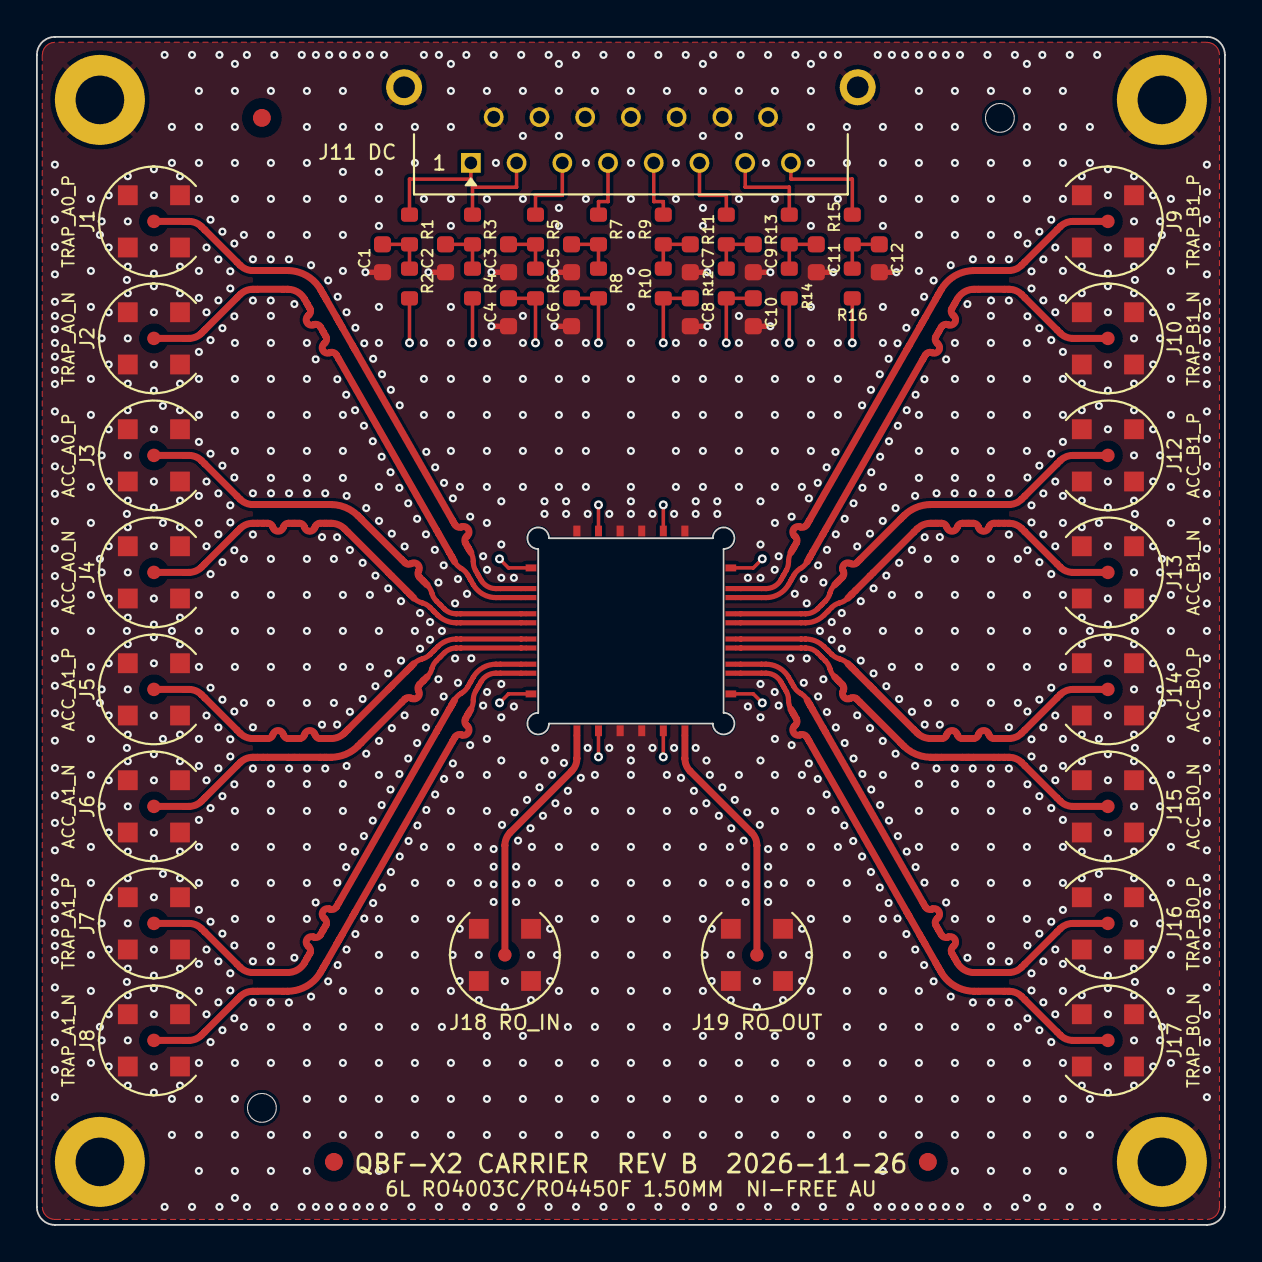
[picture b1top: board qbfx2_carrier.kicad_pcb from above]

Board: 6 copper layers, 66.0 x 66.0 mm, 57 parts (0 on the bottom side), 43 nets.

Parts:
C1, C2, C11, C12: 18p C0G; C_0603_1608Metric
C3, C4, C5, C6, C7, C8, C9, C10: 10n C0G; C_0603_1608Metric
DW1, DW2: Dowel 1.6; NPTH_Dowel_1.6mm
FID1, FID2, FID3: Fiducial; Fiducial_1.0mm_Mask2.0mm
H1, H2, H3, H4: M2.5; MountingHole_2.7mm_M2.5_Pad
J1, J2, J3, J4, J5, J6, J7, J8, J9, J10, J12, J13, J14, J15, J16, J17, J18, J19: SMP-MSLD-PCS-NM; SMP_Amphenol_SMP-MSLD-PCS-NM
J11: MWDM2L-15PCBRP-.110; MicroD_15P_Glenair_MWDM2L-15PCBRP
R1, R2, R3, R4, R13, R14, R15, R16: 1k; R_0603_1608Metric
R5, R6, R7, R8, R9, R10, R11, R12: 10k; R_0603_1608Metric
U1: QBF-X2; QBFX2_DIE_BONDPADS

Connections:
ACC_A0_N: J4.1, U1.27
ACC_A0_P: J3.1, U1.26
ACC_A1_N: J6.1, U1.29
ACC_A1_P: J5.1, U1.28
ACC_B0_N: J15.1, U1.13
ACC_B0_P: J14.1, U1.12
ACC_B1_N: J13.1, U1.11
ACC_B1_P: J12.1, U1.10
GATE_BSA_AN: C8.1, R10.2, U1.5
GATE_BSA_AN_IN: J11.5, R9.1
GATE_BSA_PREP: C6.1, R8.2, U1.2
GATE_BSA_PREP_IN: J11.4, R7.1
GATE_BSB_AN: C4.1, R6.2, U1.18
GATE_BSB_AN_IN: J11.3, R5.1
GATE_BSB_PREP: C10.1, R12.2, U1.21
GATE_BSB_PREP_IN: J11.6, R11.1
GND: C1.2, C2.2, C3.2, C4.2, C5.2, C6.2, C7.2, C8.2, C9.2, C10.2, C11.2, C12.2, H1.1, H2.1, H3.1, H4.1, J1.2, J2.2, J3.2, J4.2, J5.2, J6.2, J7.2, J8.2, J9.2, J10.2, J11.9, J11.10, J11.11, J11.12, J11.13, J11.14, J11.15, J11.SH, J12.2, J13.2, J14.2, J15.2, J16.2, J17.2, J18.2, J19.2, U1.1, U1.3, U1.4, U1.6, U1.19, U1.20
LOAD_A0: R2.2, U1.23
LOAD_A0_IN: J11.1, R1.1
LOAD_A1: R4.2, U1.32
LOAD_A1_IN: J11.2, R3.1
LOAD_B0: R14.2, U1.16
LOAD_B0_IN: J11.7, R13.1
LOAD_B1: R16.2, U1.7
LOAD_B1_IN: J11.8, R15.1
unnamed: C1.1, R1.2, R2.1
unnamed: C2.1, R3.2, R4.1
unnamed: C3.1, R5.2, R6.1
unnamed: C5.1, R7.2, R8.1
unnamed: C7.1, R9.2, R10.1
unnamed: C9.1, R11.2, R12.1
unnamed: C11.1, R13.2, R14.1
unnamed: C12.1, R15.2, R16.1
RO_IN: J18.1, U1.17
RO_OUT: J19.1, U1.22
TRAP_A0_N: J2.1, U1.25
TRAP_A0_P: J1.1, U1.24
TRAP_A1_N: J8.1, U1.31
TRAP_A1_P: J7.1, U1.30
TRAP_B0_N: J17.1, U1.15
TRAP_B0_P: J16.1, U1.14
TRAP_B1_N: J10.1, U1.9
TRAP_B1_P: J9.1, U1.8

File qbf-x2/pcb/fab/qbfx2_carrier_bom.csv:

Item,Qty,References,Value,Description,Footprint,Manufacturer,MPN,MPN status,Fitted by,Note
1,4,C1 C2 C11 C12,18p C0G,"MLCC 18 pF 5 % 50 V C0G (NP0) 0603, VJ Non-Magnetic series (termination C = Cu barrier)",qbfx2:C_0603_1608Metric,Vishay Vitramon,VJ0603A180JCAAJ,to confirm,SMT reflow (PCBA),"code built from the VJ Non-Magnetic ordering scheme, not seen listed (W1BC parts have Ni barrier)"
2,8,C3 C4 C5 C6 C7 C8 C9 C10,10n C0G,"MLCC 10 nF 5 % 50 V C0G (NP0) 0603, VJ Non-Magnetic series (termination C = Cu barrier)",qbfx2:C_0603_1608Metric,Vishay Vitramon,VJ0603A103JCAAJ,to confirm,SMT reflow (PCBA),"code built from the VJ Non-Magnetic ordering scheme, not seen listed; if 10 nF/0603 is not offered use 1 nF (gate f-3dB 5.96 kHz, still <= 10 kHz) or a Knowles Syfer non-magnetic C0G"
3,4,H1 H2 H3 H4,M2.5,"Mounting hole 2.7 mm plated, GND",qbfx2:MountingHole_2.7mm_M2.5_Pad,-,-,mechanical,"board feature, not purchased","board feature, not purchased"
4,18,J1 J2 J3 J4 J5 J6 J7 J8 J9 J10 J12 J13 J14 J15 J16 J17 J18 J19,SMP-MSLD-PCS-NM,"SMP straight PCB jack, surface mount, limited detent, non-magnetic (BeCu/Au, LCP)",qbfx2:SMP_Amphenol_SMP-MSLD-PCS-NM,Amphenol RF,SMP-MSLD-PCS-NM,confirmed,SMT reflow (PCBA),non-magnetic; land pattern generic - confirm against the Amphenol drawing
5,1,J11,MWDM2L-15PCBRP-.110,"Micro-D 15-pin plug, condensed right-angle PCB, jackposts",qbfx2:MicroD_15P_Glenair_MWDM2L-15PCBRP,Glenair,MWDM2L-15PCBRP-.110,confirmed,hand solder after reflow (PCBA),land pattern + shell finish TO CONFIRM (ask for a non-magnetic shell finish)
6,8,R1 R2 R3 R4 R13 R14 R15 R16,1k,"Thin-film resistor 1 kOhm 0.1 % 25 ppm 0603, non-magnetic (PNM series)",qbfx2:R_0603_1608Metric,Vishay Dale Thin Film,PNM0603E1001BST5,confirmed,SMT reflow (PCBA),distributor listing found; same series as the 10 kOhm part
7,8,R5 R6 R7 R8 R9 R10 R11 R12,10k,"Thin-film resistor 10 kOhm 0.1 % 25 ppm 0603, non-magnetic (PNM series)",qbfx2:R_0603_1608Metric,Vishay Dale Thin Film,PNM0603E1002BST5,confirmed,SMT reflow (PCBA),distributor listing: 10 kOhm 0.1 % 0603 non-magnetic
8,1,U1,QBF-X2,"QBF-X2 superconducting die 10 x 10 x 0.525 mm, wire-bonded (32 launchers, die_pads.json rev B)",qbfx2:QBFX2_DIE_BONDPADS,QBF-X2 project,QBF-X2 die rev per circuits/,customer supplied,customer: die attach + wire bond,not part of PCBA; die attach + Al wedge bonding after assembly

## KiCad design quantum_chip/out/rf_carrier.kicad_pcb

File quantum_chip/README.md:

# QFX-1: a quantum-fluxon chip on a 6-layer RF carrier

QFX-1 is a superconducting processor die whose qubits are **quantum fluxons**: single Josephson vortices that tunnel
between two wells in a ring of 24 tiny junctions. A second kind of fluxon gates them: a heavy, classical one that flies
past on a ballistic line and leaves with its energy.

- **Carrier:** the die is wire-bonded into a red-mask, 6-layer Rogers RF carrier (KiCad 7) on a gold-plated copper
  package.
- **3D model:** every layer is extruded from the exported CAD polygons, rendered in Blender Cycles, and explorable in a
  browser.
- **Single source:** one parameter file, `src/design_params.py`, drives everything through `./build_all.sh`.

What is new compared with the literature, and what is not, is in **[docs/NOVELTY.md](docs/NOVELTY.md)**. Short
version: a single quantum-fluxon qubit has been demonstrated before (KIT, 2023). Gating it with another fluxon, the
momentum rule for that gate, and two coupled fluxon qubits on one chip are what we did not find. Nothing here has been
fabricated or measured.

**Follow-on project: [QBF-X2](../qbf-x2/README.md).** Here both fluxons are quantum and flying: two dual-rail fluxon
qubits are entangled by a collision. That repository also simulates a Bell pair between the two QFX-1 qubits on this
chip (companion device 1).

## How it works

1. **Qubit.** One fluxon (a 2π phase kink carrying one flux quantum Φ0) is trapped in a closed ring of 24 small
   Al/AlOx/Al junctions, joined by granular-aluminium superinductors.
   - Two weaker junctions, two cells apart, make two wells for the fluxon. The junction between them is a dc SQUID that
     sets the tunnelling barrier.
   - |0⟩ and |1⟩ are the symmetric and antisymmetric superpositions of "fluxon in the left well" and "fluxon in the
     right well".
2. **Gate.** A DC/SFQ converter launches a heavy fluxon into an unbiased 7.8 mm ballistic line of 783 large junctions.
   - While it crosses a 1.2 mm section, a flux transformer tilts the qubit's double well, and the qubit picks up a
     conditional phase (Z rotation).
   - The fluxon keeps going and is detected by an SFQ/DC converter. The line itself carries no bias and dissipates
     nothing.
3. **Rule.** The heavy fluxon is delayed by an amount that depends on the qubit state: δX = ħθ/p. A gate is clean only
   if the fluxon's momentum is large compared with its thermal spread.
4. **Coupling and readout.** The two rings share a small inductance (a galvanic bus). Each ring shares 40 pH with a
   λ/4 resonator on a common feedline for dispersive readout. Drive lines tilt the wells at microwave rates.
5. **Double sweet spot.** At zero SQUID flux, f01 is first-order insensitive to both barrier-flux and tilt-flux noise.

```
  north pads:  VB_IN   KICK_TRIG        QF1_FLUX   QF2_FLUX        KICK_OUT   VB_OUT
                         DC/SFQ ┐                                    ┌ SFQ/DC
                                │ heavy-fluxon line: 783 JJ, 7.8 mm, │
                                │ Nb CPW 20 µm strip / 1 µm gaps     │
                                └──[ section 1: 1.2 mm ]──[ section 2: 1.2 mm ]──┘
                                         ║ XFMR1 (flared)    ║ XFMR2 (flared)
  QF1_DRIVE ──────────────────────── (QF1) ═════ BUS ═════ (QF2) ──────────────────────── QF2_DRIVE
                                       │ RES1 7.0 GHz        │ RES2 7.4 GHz
  FEED_IN ─────────────────────────────┴── readout feedline ─┴──────────────────────────── FEED_OUT
```

## Physics (`src/qfx_sim.py` → `out/qfx_sim.json`)

**Model.**
- *Ring spectrum:* the minimum-energy path of the 24-junction ring between the two wells (string method in
  mass-weighted phases), then a 1D Schrödinger equation along that path. It is checked against the full 24-junction
  normal modes.
- *Gate:* 24-level qubit dynamics under the kink-shaped, tapered tilt pulse. The transformer coupling κ is calibrated
  by bisection for θ = π/2.
- *Back-action:* a classical discrete sine-Gordon simulation of the line with the qubit-dependent interaction.

| Quantity | Value |
|---|---|
| Ring cell | E_J = 39.7 GHz (I_c = 79.9 nA), E_C = 8.07 GHz (C = 2.40 fF), E_L = E_J (Λ = 1, 4.12 nH of grAl per cell) |
| Double well | two pinning junctions at 0.3·E_J; barrier dc SQUID with E_J,max = 1.35·E_J |
| Operating point Φ_b = 0 | **f01 = 3.208 GHz, f12 = 17.19 GHz**, f02 = 20.40 GHz, barrier 23.5 GHz |
| Tuning | f01 from 3.21 GHz (Φ_b = 0) up to 27.5 GHz (Φ_b = 0.48 Φ0) |
| Flux noise | df01/dΦ_b = 0 at the operating point, against up to 81 GHz/Φ0 on the slope. Tilt couples only transversally (G00 − G11 = 5×10⁻⁹) |
| Model check | pinning mode 32.763 GHz from the path vs 32.768 GHz from the full Hessian (0.015 %). Next internal mode 51.1 GHz, so the fluxon motion separates from the array modes |
| Drive and tilt | flux on one barrier link: G01 = 125 GHz/Φ0 (the transformer lands here). Differential flux across both barrier links: G01 = 249 GHz/Φ0, well tilt dε/dΦ = 625 GHz/Φ0 |
| Qubit–qubit coupling | J = L_s·ΔI²/4 = **3.79 MHz per pH** of shared inductance (ΔI = 100 nA). ZZ in the fluxon-position basis, XX in the energy basis at the sweet spot |
| Readout | 40 pH shared with a 7.0 GHz λ/4: g = 70.6 MHz, χ ≈ 1.3 MHz |
| Kick line | I_c = 20 µA, C = 600 fF, f_p = 50.65 GHz. CPW 20/1 µm gives 0.229 pH/µm → L_cell = 2.29 pH at 10 µm pitch vs L_J = 16.46 pH → Λ = 2.68 cells. c0 = 8.53 µm/ps; rest energy 213 THz·h |
| **Kick gate** (v = 0.05 c0) | 1.2 mm section with 200 µm raised-cosine ramps (2.34 ns effective dwell), κ = 2.55×10⁻³ → phase **1.5706 rad**, bit-flip **7.7×10⁻⁷**, leakage 2.6×10⁻¹² |
| **Back-action** | δX = ħθ/p: 2.008 cells (sine-Gordon) vs 2.001 cells (formula), 0.4 %. Thermal which-path dephasing per π/2 gate at 20 mK: **9.7×10⁻⁴** at 0.05 c0. Launch-speed jitter must stay below 0.9 % for a 10⁻⁴ phase error |

Kick speed trade-off, π/2 gate at 20 mK. The kinetic energy KE is ½·E0·β². Only v = 0.05 c0 was run through the full
dynamics:

| v / c0 | v (µm/ps) | dwell (ns) | KE (GHz·h) | which-path dephasing |
|---|---|---|---|---|
| 0.01 | 0.085 | 11.7 | 10.7 | 2.4×10⁻² |
| 0.02 | 0.171 | 5.86 | 42.6 | 6.0×10⁻³ |
| **0.05** | **0.427** | **2.34** | **267** | **9.7×10⁻⁴** |
| 0.1 | 0.853 | 1.17 | 1074 | 2.4×10⁻⁴ |
| 0.2 | 1.707 | 0.59 | 4394 | 6×10⁻⁵ |

## The die (`out/quantum_die.gds`, cell `QFX1`)

**Process stack.** Substrate: 525 µm high-resistivity Si.

| Layer (GDS) | Material | Thickness | Contents |
|---|---|---|---|
| BASE (1/0) | Nb | 150 nm | ground plane, feedline, λ/4 resonators, drive and flux lines, kick-line strip, transformers, bus, pads |
| GRAL (2/0) | granular Al | 20 nm | ring superinductor rails (≈0.5 nH/□) |
| AL1 (3/0) | Al | 30 nm | bottom electrodes (first evaporation angle) |
| AlOx | AlOx | ~2 nm | tunnel barrier; a junction is AL1 ∧ AL2 |
| AL2 (4/0) | Al | 60 nm | top electrodes (second angle) |
| RES (5/0) | Cu | 50 nm | converter shunt and bias resistors, quasiparticle traps |
| ABP / ABS (6/0, 7/0) | Al | 3 µm posts / 400 nm spans | 10 airbridges where lines cross |
| 63/0, 64/0 | (documentation) | — | route centre lines; patches that tie line ends to ground (validation removes them to test isolation) |

**Junctions.** All 837 come from one Al/AlOx/Al step (Jc = 1.665 µA/µm², 50 fF/µm²), so each area fixes both I_c and
C:

| Junction | Count | Area | I_c | C |
|---|---|---|---|---|
| ring rung | 42 | 0.048 µm² | 80 nA | 2.40 fF |
| pinning (well) | 4 | 0.0144 µm² | 24 nA | 0.72 fF |
| barrier SQUID | 4 | 0.0324 µm² | 54 nA | 1.62 fF |
| kick line | 783 | 12.0 µm² | 20 µA | 600 fF |
| DC/SFQ + SFQ/DC | 4 | 12.0 µm² | 20 µA | 600 fF |

The kick-line junctions overlap the strip edge: AL1 wraps the strip edge and AL2 crosses the 1 µm gap onto ground.

The readout resonators are 4291.3 µm (7.0 GHz) and 4059.2 µm (7.4 GHz), with ε_eff = (ε_r + 1)/2.

## The carrier

40 × 40 × 1.496 mm, 6-layer RO4003C/RO4450F, ENIG, red LPI mask.

- **Top side:** F.Cu GCPW (0.43/0.20 mm, 49.9 Ω) carries KICK_TRIG, KICK_OUT, QF1/QF2_DRIVE and FEED_IN/OUT to six
  end-launch SMAs.
- **Bottom side:** VB_IN, VB_OUT (converter bias) and QF1/QF2_FLUX (fluxon trapping and barrier trim) run bond pad →
  blind via → In2 stripline (49.3 Ω) → blind via → B.Cu → four bottom SMPs.
- **Ground:** In1/In3 are solid ground around the stripline, and 324 stitching vias tie the planes together.
- **Bonds:** 20 signal bonds (two per pad) and 67 ground bonds onto the die ground.
- **KiCad DRC:** 0 violations, 0 unconnected items.

## Deliverables

| Requested | File |
|---|---|
| quantum_die.gds | `out/quantum_die.gds` (cell `QFX1`), KLayout previews `docs/die_preview*.png` |
| rf_carrier.kicad_pcb | `out/rf_carrier.kicad_pcb` + `.kicad_pro` / `.kicad_dru`, Gerbers + drill (blind spans separate), SVG |
| assembly.step | `out/assembly.stpZ` (gzip STEP AP214, named parts, true thicknesses); `out/rf_carrier.step` (KiCad board body) |
| quantum_assembly.blend | `out/quantum_assembly.blend` |
| layer_stack.yaml / connections.json | `out/layer_stack.yaml`, `out/connections.json` |
| renders | `renders/assembled_chip.png`, `red_pcb_view.png`, `exploded_layers.png`, `internal_trace_cutaway.png`, `quantum_fluxon_macro.png`, `wirebond_macro.png`, `technical_cad_view.png` |
| interactive_3d_view.html | `out/interactive_3d_view.html` + `out/assembly.glb` (serve the folder: `cd out && python3 -m http.server`) |
| physics | `out/qfx_sim.json`, `docs/qfx_sim.png` |
| validation | `docs/VALIDATION.md`: **86 checks, 86 pass**. Covers PCB continuity and DRC, die netlist from the GDS, the single junction process, fluxon physics, the gate and back-action, bonds, the stack, and 2D↔3D consistency |
| novelty | `docs/NOVELTY.md`: prior art, what is new, and how the search was done |

Earlier designs stay in the pipeline:
- the reversible-fluxon-logic die RFL-RE1: set `ACTIVE_DIE = "RFL"`;
- the 4-transmon die: `src/build_die_transmon.py`.

## Not settled (read before fabricating)

**Not simulated:**
- the EM coupling of the flared transformers (κ = 2.55×10⁻³ is a target; the raised-cosine profile stands in for the
  flare), the bus and the readout taps — extract them with Sonnet, InductEx or similar;
- the DC/SFQ and SFQ/DC converters (cell layouts are placeholders; run JoSIM or WRspice);
- the real launch-speed spread of the converter;
- T1 and T2: no noise or loss model beyond the which-path back-action;
- quasiparticles and radiation in the 7.8 mm line.

**Loading the fluxon:** one Φ0 has to be trapped in each ring, by field-cooling or by a pulse on QFx_FLUX with the
barrier lowered. This is not modelled.

**Fabrication spread:** f01 depends steeply on the barrier junction (f01 rises from 3.2 to 3.9 GHz when E_J,max drops
from 1.35 to 1.30·E_J), and the SQUID can only raise f01. Aim the barrier junction slightly large and trim with flux,
moving off the exact sweet spot. The grAl inductance (Λ = 1) also varies run to run.

**Kick line:** Λ comes from closed-form CPW formulas (Nb λ_L = 90 nm). The junctions sit on the strip edge, which
needs an ion-mill contact. The Peierls–Nabarro barrier at Λ = 2.7 is negligible, but losses at 20 mK are assumed
negligible, not computed.

**Carrier:**
- ENIG contains magnetic nickel; use a Ni-free finish near the die.
- Flux trapping calls for magnetic shielding and ground-plane moats, which are not drawn.
- The connectors are generic, not vendor parts, and the line impedances are closed-form.

**Display exaggeration:** films under 3 µm are drawn thicker in the GLB and the .blend so they can be seen. The STEP
and the thickness readouts use the true values, and XY geometry is never changed.

## References (full prior-art table in docs/NOVELTY.md)

- A. Wallraff et al., "Quantum dynamics of a single vortex", *Nature* 425, 155 (2003).
- KIT PhD thesis, "Quantum Tunneling of Josephson Vortices in High-Impedance Long Junctions" (2023), doi:10.5445/IR/1000158804; M. Wildermuth et al., *Appl. Phys. Lett.* (2022), doi:10.1063/5.0082197.
- S. S. Seidov, M. V. Fistul, "Quantum dynamics of a single fluxon in Josephson junctions parallel arrays with large kinetic inductances", *Phys. Rev. A* 103, 062410 (2021).
- D. V. Averin, K. Rabenstein, V. K. Semenov, "Rapid ballistic readout for flux qubits", *Phys. Rev. B* 73, 094504 (2006).
- K. D. Osborn, W. Wustmann, "Reversible Fluxon Logic", arXiv:1711.04339; W. Wustmann, K. D. Osborn, fluxon-transmission readout, arXiv:2504.18915.
- S. Matsuo et al., "Fluxon-based gate controls of capacitively coupled flux-based-phase qubits", *Appl. Phys. Lett.* 91, 093103 (2007).
- M. V. Fistul, A. V. Ustinov, "Josephson vortex interaction mediated by cavity modes", *Phys. Rev. B* 68, 132509 (2003).
- S. Huang et al., "Microwave Package Design for Superconducting Quantum Processors", *PRX Quantum* 2, 020306 (2021).

## Tools

- KLayout 0.30: die layout and previews.
- KiCad 7.0: board, DRC, Gerber and STEP.
- numpy/scipy: our own string-method, multilevel-dynamics and discrete sine-Gordon solvers.
- OpenCascade/OCP: assembly STEP.
- trimesh: GLB.
- Blender 5.3 Cycles via `bpy`: renders.
- three.js 0.160: viewer.

Literature search: Undermind, Lune, alphaXiv, SciSpace, Valency and Paperguide; unit checks in Wolfram|Alpha. See
docs/NOVELTY.md.

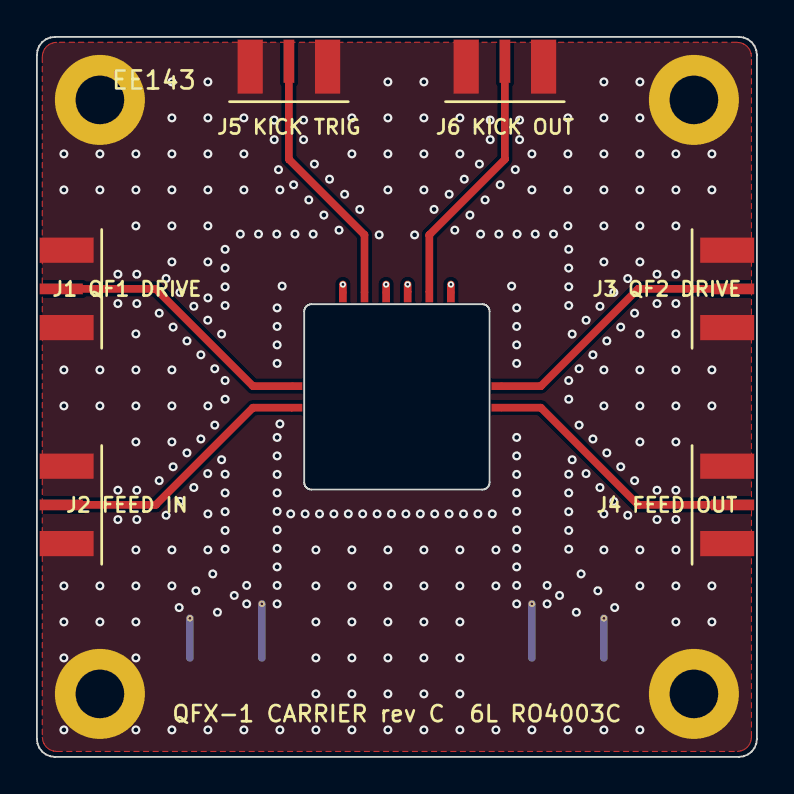
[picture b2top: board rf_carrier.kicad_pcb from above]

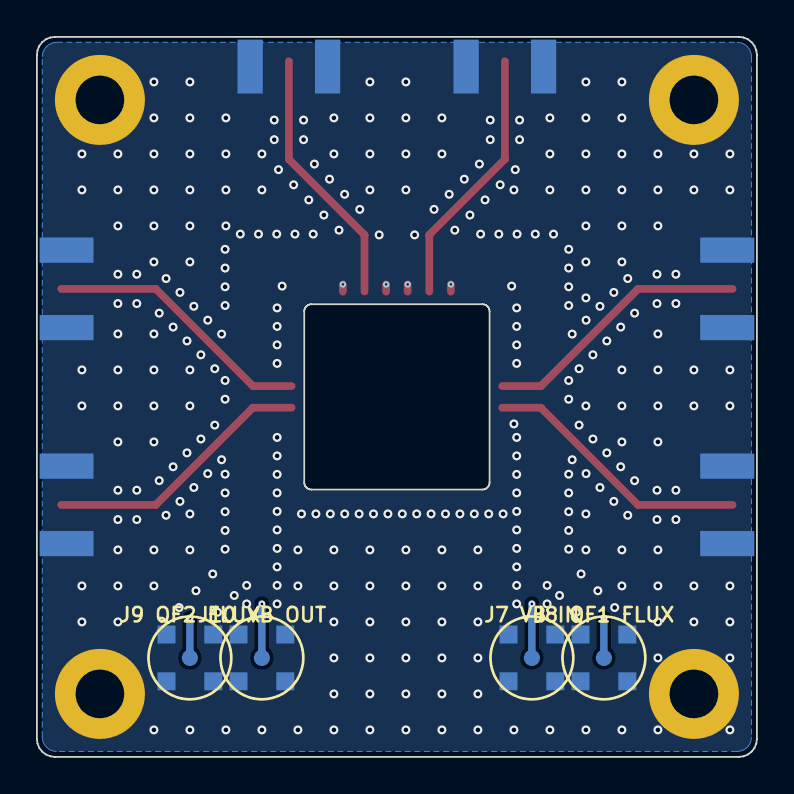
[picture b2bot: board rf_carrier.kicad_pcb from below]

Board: 6 copper layers, 40.0 x 40.0 mm, 24 parts (4 on the bottom side), 11 nets.

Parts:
BP1, BP2, BP3, BP4, BP5, BP6, BP7, BP8, BP9, BP10: BOND_PAD
H1, H2, H3, H4: M2.5; MountingHole_2.7mm_M2.5_Pad
J1, J2, J3, J4, J5, J6: SMA_EDGE
J7, J8, J9, J10: SMP_VERT_BOTTOM

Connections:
FEED_IN: BP9.1, J2.1
FEED_OUT: BP8.1, J4.1
GND: H1.1, H2.1, H3.1, H4.1, J1.2, J2.2, J3.2, J4.2, J5.2, J6.2, J7.2, J8.2, J9.2, J10.2
KICK_OUT: BP5.1, J6.1
KICK_TRIG: BP2.1, J5.1
QF1_DRIVE: BP10.1, J1.1
QF1_FLUX: BP3.1, J8.1
QF2_DRIVE: BP7.1, J3.1
QF2_FLUX: BP4.1, J9.1
VB_IN: BP1.1, J7.1
VB_OUT: BP6.1, J10.1

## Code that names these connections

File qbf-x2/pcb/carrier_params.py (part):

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MICROD = dict(x=0.0, y_row1=26.0, pitch=2.54, row_dy=2.54, drill=0.70, pad=1.10,
              mount_dx=12.6, mount_y=26.0 + 4.2, mount_drill=1.20, mount_pad=2.0)   # mount_y = y_row1 + 4.2 (board y)
# J11 pin assignment (pins 1..8 = filtered DC inputs, row 1; 9..15 = GND returns, row 2)
MICROD_PINS = {1: "LOAD_A0", 2: "LOAD_A1", 3: "GATE_BSB_AN", 4: "GATE_BSA_PREP",
               5: "GATE_BSA_AN", 6: "GATE_BSB_PREP", 7: "LOAD_B0", 8: "LOAD_B1"}

# RF connector nets in schematic order (west column top -> bottom, east column top -> bottom, readout) and their
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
